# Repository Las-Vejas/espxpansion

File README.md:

# espxpansion

This is an expansion module for the [Hackxpansion console](https://github.com/hackclub/hackxpansion) which adds the ESP32-C6-MINI.

The ESP can communicate to the Console using UART. There is also a breakout on the side of the board with the UART pins along with power and ground pins. programming can also be done via uart.
There are also buttons for boot and reset.

The case is 3d printed, and uses 2 M2 screws to screw into the pcb.

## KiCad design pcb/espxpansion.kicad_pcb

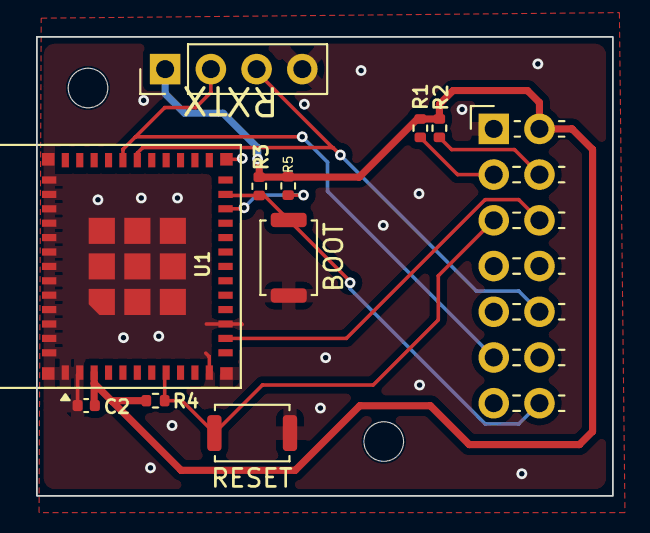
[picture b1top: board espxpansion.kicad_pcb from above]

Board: 2 copper layers, 32.0 x 25.5 mm, 11 parts (0 on the bottom side), 10 nets.

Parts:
BOOT: BOOT; SW_Push_SPST_NO_Alps_SKRK
C2: 10uF; C_0402_1005Metric
J1: Male_Module
J2: Conn_01x02_Pin; PinHeader_1x04_P2.54mm_Vertical
R1: 1k; R_0402_1005Metric
R2: 20k; R_0402_1005Metric
R3, R4, R5: 10k; R_0402_1005Metric
RESET: RESET; SW_Push_SPST_NO_Alps_SKRK
U1: ESP32-C6-MINI-1

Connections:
+3V3: C2.1, J1.2 (3V3), J2.1, R1.1, R2.1, R3.1, R4.1, R5.1, U1.3 (3V3)
/BOOT: BOOT.2, J1.14 (GPIO9), R3.2, U1.23 (IO9)
/EN: J1.5 (I2C_SCL), R4.2, RESET.2, U1.8 (EN)
/ESP_RX: J1.10 (UART_TX), J2.3, U1.30 (RXD0)
/ESP_TX: J1.11 (UART_RX), J2.2, U1.31 (TXD0)
GND: BOOT.1, C2.2, J1.1 (GND), J2.4, RESET.1, U1.1 (GND), U1.2 (GND), U1.11 (GND), U1.14 (GND), U1.36 (GND), U1.37 (GND), U1.38 (GND), U1.39 (GND), U1.40 (GND), U1.41 (GND), U1.42 (GND), U1.43 (GND), U1.44 (GND), U1.45 (GND), U1.46 (GND), U1.47 (GND), U1.48 (GND), U1.49 (GND), U1.50 (GND), U1.51 (GND), U1.52 (GND), U1.53 (GND)
unnamed: J1.6 (I2C_SDA), U1.13 (IO1)
unnamed: J1.3 (MD0), R1.2
unnamed: J1.4 (MD1), R2.2
unnamed: R5.2, U1.22 (IO8)

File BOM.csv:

Reference,Price,Qty,Value,LCSC Part #
C1,0.50 $US,1,100nF,C60474
C2,1.41 $US,1,10uF,C76991
J1,0.00 $US,1,N/A,N/A
J2,0.00 $US,1,Conn_01x02_Pin,N/A
R1,0.15 $US,1,1k,C140197
R2,0.18 $US,1,20k,C2906867
"R3,R4,R5",0.24 $US,3,10k,C2906861
"SW1, SW2",0.50 $US,1,BOOT,C720477
U1,3.93 $US,1,ESP32-C6-MINI-1,C5736265
PCB,4.00 $US,5,N/A,N/A
Stencil,3.07 $US,1,N/A,N/A
TOTAL,13.98 $US,N/A,N/A,N/A
